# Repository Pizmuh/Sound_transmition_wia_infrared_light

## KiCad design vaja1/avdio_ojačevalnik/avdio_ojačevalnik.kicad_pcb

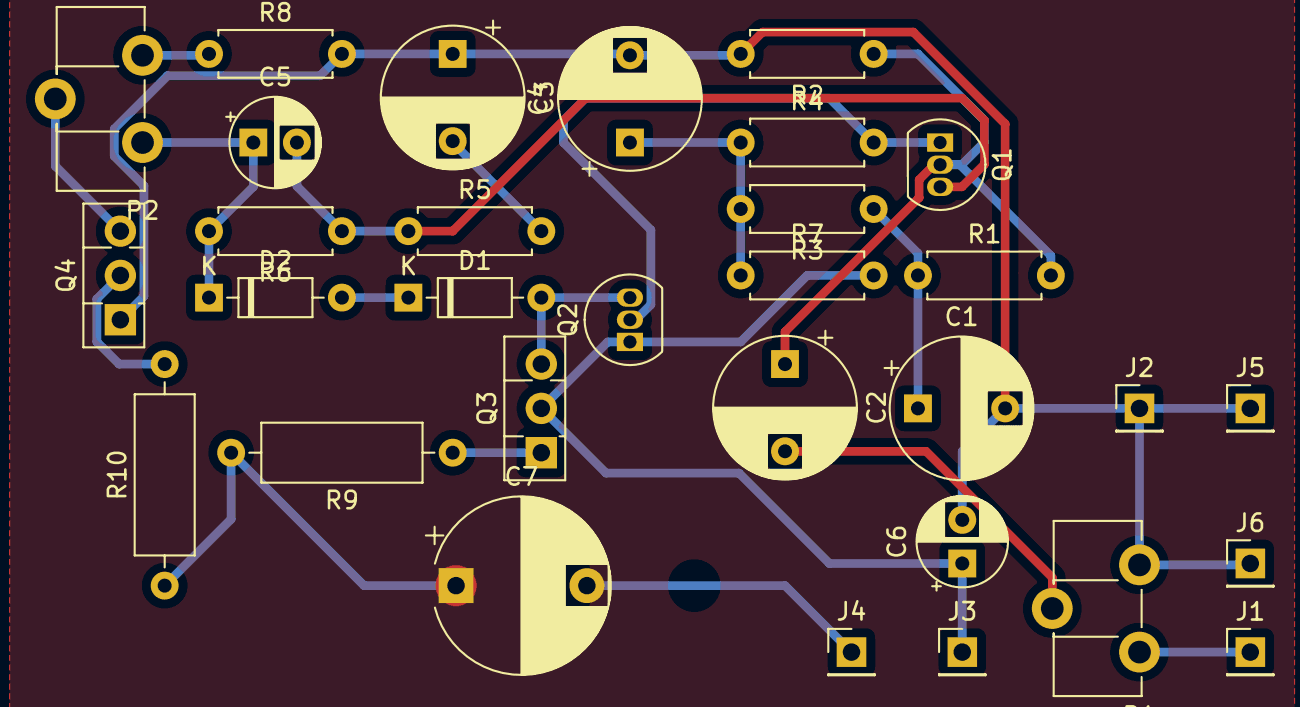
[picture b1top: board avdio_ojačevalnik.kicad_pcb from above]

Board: 2 copper layers, 31 parts (0 on the bottom side), 19 nets.

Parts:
C1: 470µF; CP_Radial_D8.0mm_P5.00mm
C2: 100nF; CP_Radial_D8.0mm_P5.00mm
C3: 330µF; CP_Radial_D8.0mm_P5.00mm
C4: 220µF; CP_Radial_D8.0mm_P5.00mm
C5: 150pF; CP_Radial_D5.0mm_P2.50mm
C6: 100µF; CP_Radial_D5.0mm_P2.50mm
C7: 220µF; CP_Radial_D10.0mm_P7.50mm
D1, D2: 1N4148; D_DO-35_SOD27_P7.62mm_Horizontal
J1, J2, J3, J4, J5, J6: Conn_01x01_Female; PinHeader_1x01_P2.54mm_Vertical
P1: 100k; Potentiometer_ACP_CA9-H5_Horizontal
P2: 470; Potentiometer_Piher_PT-10-H05_Horizontal
Q1: BC547; TO-92_Inline
Q2: BC558; TO-92_Inline
Q3: BD139; TO-126-3_Vertical
Q4: BD140; TO-126-3_Vertical
R1, R3: 27k; R_Axial_DIN0207_L6.3mm_D2.5mm_P7.62mm_Horizontal
R2: 100k; R_Axial_DIN0207_L6.3mm_D2.5mm_P7.62mm_Horizontal
R4: 12k; R_Axial_DIN0207_L6.3mm_D2.5mm_P7.62mm_Horizontal
R5: 1k; R_Axial_DIN0207_L6.3mm_D2.5mm_P7.62mm_Horizontal
R6: 22k; R_Axial_DIN0207_L6.3mm_D2.5mm_P7.62mm_Horizontal
R7: 330; R_Axial_DIN0207_L6.3mm_D2.5mm_P7.62mm_Horizontal
R8: 1k8; R_Axial_DIN0207_L6.3mm_D2.5mm_P7.62mm_Horizontal
R9, R10: 1; R_Axial_DIN0309_L9.0mm_D3.2mm_P12.70mm_Horizontal

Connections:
Earth: C1.2, C3.1, C4.2, C6.2, J2.1, J5.1, J6.1, P1.3, Q4.1, R2.2, R8.2
unnamed: C1.1, R1.1, R3.1
unnamed: C2.1, Q1.2, R1.2, R2.1
unnamed: C2.2, P1.2
unnamed: C3.2, R5.2
unnamed: C4.1, R3.2, R4.1, R7.1
unnamed: C5.1, D2.1, P2.1, R6.2
unnamed: C5.2, Q1.3, R5.1, R6.1
unnamed: C6.1, J3.1, Q2.1, Q3.2, R7.2
unnamed: C7.1, R9.2, R10.1
unnamed: C7.2, J4.1
unnamed: D1.1, D2.2
unnamed: D1.2, Q2.3, Q3.3
unnamed: J1.1, P1.1
unnamed: P2.2, Q4.3
unnamed: P2.3, R8.1
unnamed: Q1.1, Q2.2, R4.2
unnamed: Q3.1, R9.1
unnamed: Q4.2, R10.2

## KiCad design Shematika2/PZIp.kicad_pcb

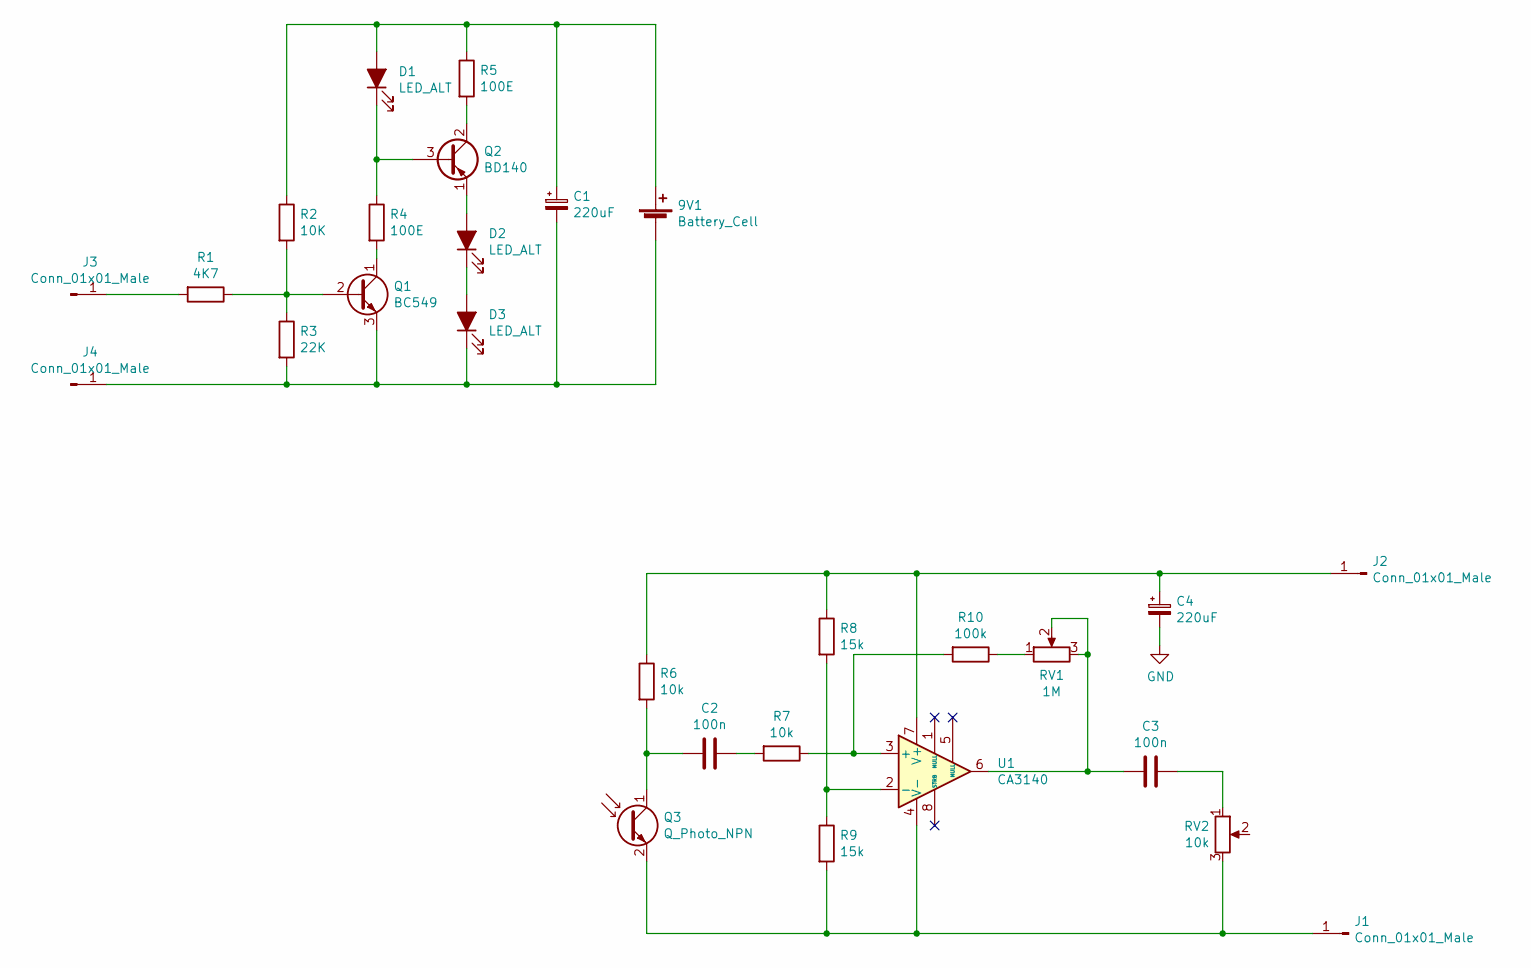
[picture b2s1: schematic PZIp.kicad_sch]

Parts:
9V1: Battery_Cell
C1, C4: 220uF
C2, C3: 100n
D1, D2, D3: LED_ALT
J1, J2, J3, J4: Conn_01x01_Male
Q1: BC549; TO-92_Inline
Q2: BD140; TO-126-3_Vertical
Q3: Q_Photo_NPN
R1: 4K7
R2: 10K
R3: 22K
R4, R5: 100E
R6, R7: 10k
R8, R9: 15k
R10: 100k
RV1: 1M
RV2: 10k
U1: CA3140

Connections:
GND: C4.2
unnamed: 9V1.1 (+), C1.1, D1.2 (A), R2.1, R5.1
unnamed: 9V1.2 (-), C1.2, D3.1 (K), J4.1, Q1.3 (E), R3.2
unnamed: C2.1, R7.2
unnamed: C2.2, Q3.1 (C), R6.2
unnamed: C3.1, RV2.1
unnamed: C3.2, RV1.2, RV1.3, U1.6
unnamed: C4.1, J2.1, R6.1, R8.1, U1.7 (V+)
unnamed: D1.1 (K), Q2.3 (B), R4.1
unnamed: D2.1 (K), D3.2 (A)
unnamed: D2.2 (A), Q2.1 (E)
unnamed: J1.1, Q3.2 (E), R9.2, RV2.3, U1.4 (V-)
unnamed: J3.1, R1.2
unnamed 13: RV2.2; also elsewhere on the board
unnamed: Q1.1 (C), R4.2
unnamed: Q1.2 (B), R1.1, R2.2, R3.1
unnamed: Q2.2 (C), R5.2
unnamed: R8.2, R9.1, U1.2 (-)
unnamed: R10.1, RV1.1
unnamed: R7.1, R10.2, U1.3 (+)

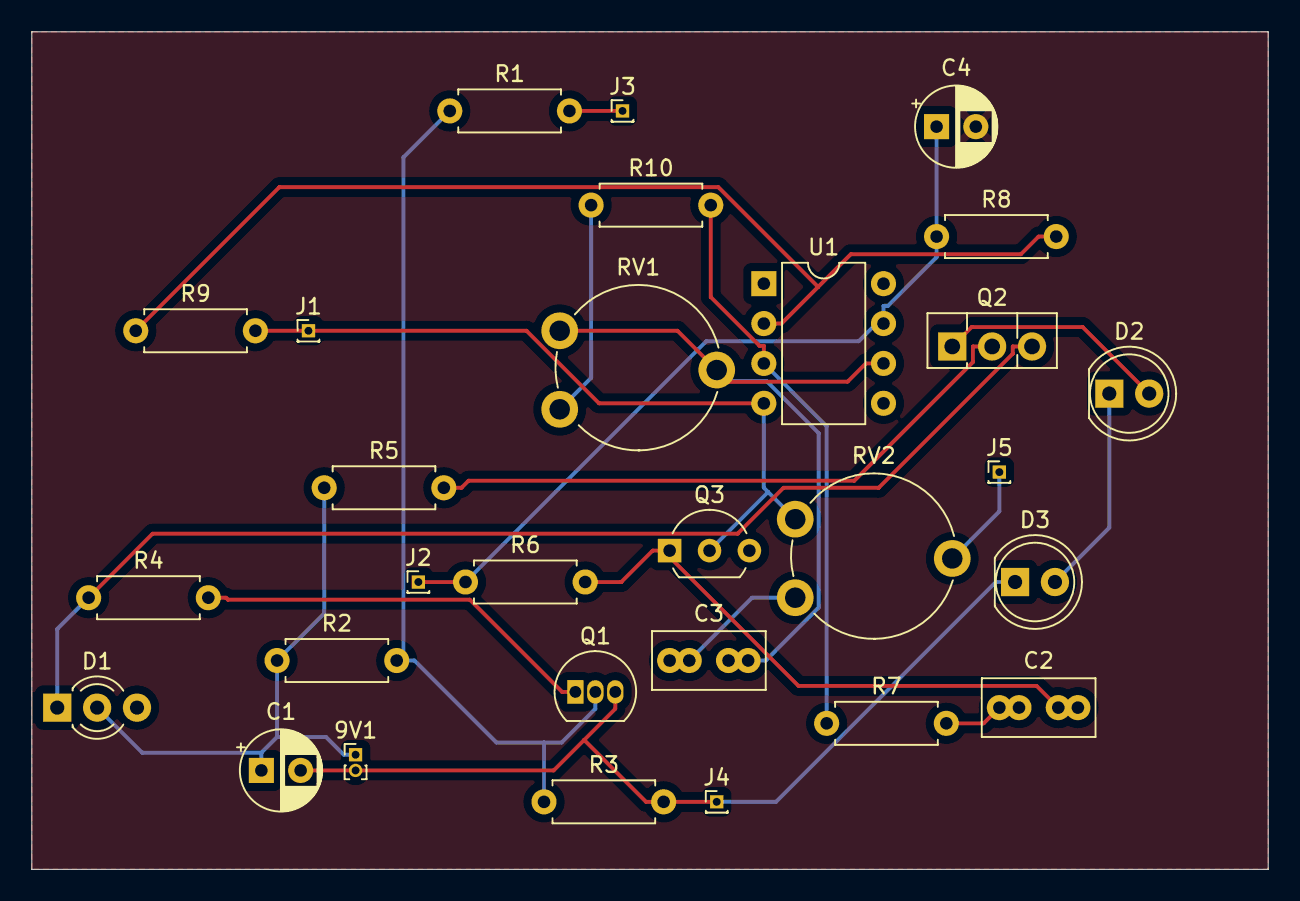
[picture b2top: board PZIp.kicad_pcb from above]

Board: 2 copper layers, 78.7 x 53.3 mm, 29 parts (0 on the bottom side), 19 nets.

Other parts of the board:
J5: Conn_01x01_Male; PinHeader_1x01_P1.00mm_Vertical

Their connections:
unnamed 13: J5.1; also elsewhere on the board
